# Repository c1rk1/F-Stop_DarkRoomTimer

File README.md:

# F-Stop DarkRoom Timer
Simple to build, simple to use "F-Stop" DarkRoom Timer. 
- F-Stop-s  1/1, 1/2, 1/3, 1/4, 1/6, 1/12
- Strip expo feature - 3, 5, 7, 9 strips
- Zone expo feature, from 5 to 15 zones for dodge and burn
- develop timer feature - 1-900sec (15min)

F- stop printing was originally made popular by the award winning printer Gene Nocon in 1987. 

Menu options:
*  En.-t. : Enlarger timer
*  dE.-t. : Develop timer
*  SEt.t. : Set time
*  F-St.  : f-stop set
*  Stri.  : Strip
*  Zone   : Zone expo

En.-t. : Enlarger timer - set the desired value with the rotary encoder (the steps can be set in "F-St." menu) START/Pause with the "Pedal button". Sound will be played on lamp ON and lamp OFF. Default value after power up 10 sec. (you can change it in "SEt.t." menu).

dE.-t. : Develop timer - a simple count down timer in sec. from max 900 to 0 (default after power up 180sec/ 3min) Use rotary encoder to change the value, push long (1sec) to toggle between 1x/10x. Sound will play on begin and end. Start/pause with pedal button.

SEt.t. : Set time - of the enlarger timer start/begining value (0.1-10.0)  default is 10 sec. Use the rotary encoder to change the value, short press to select and go back. This will have effect in "En.-t. : Enlarger timer" menu.

F-St.  : f-stop set - set the steps what you want to use (1/1, 1/2, 1/3, 1/4, 1/6, 1/12 This will have effect in "En.-t. : Enlarger timer" and "Stri.  : Strip" menu

Stri.  : Strip - an easy way to create test strip. First set the estimated exprosure time in "En.-t. : Enlarger timer" menu then in the "Stri.  : Strip" menu select the count of the strips you want (3, 5, 7, 9). It will display ex. "S.-5" from Strip-5. To procced, long press the rotary encoder and the display will show blinking number 1. If you are ready press pedal/START button and exprosure will be made, continue while all strip is done - according to the selected count.
So for example 5. you will have 2 under exprosure and 2 over exprosure and in the middle the estimated value in  "En.-t. : Enlarger timer" menu. Ex: you estimated 10sec in  "En.-t. : Enlarger timer" menu and selected 1/2 F-Stops in "F-St.  : f-stop" menu and S.-5 (five strips). This will be:
1. strip = 5.0sec
2. strip + 2.1sec to previous (total 7.1sec)
3. strip + 2.9sec to previous (total 10.0sec - the middle, what you selected  in  "En.-t. : Enlarger timer" menu)
4. strip + 4.1sec to previous (total 14.1sec)
5. strip + 5.9sec to previous (total 20.0sec)

After developing the paper (use dE.-t. : Develop timer) select the best exprosure time what you can set it in "En.-t. : Enlarger timer" menu.

Zone   : Zone expo is very similar in use to Strip menu but the Zones (sequences) can be select from 5-15. The total expo time will be the time selected in "En.-t. : Enlarger timer" menu and the steps will be F-Stops selected in "F-St.  : f-stop" menu.

Example: you set 20sec in  "En.-t. : Enlarger timer" menu and selected 1/2 F-Stops in "F-St.  : f-stop" menu and Z.-5 (five zone). This will be:
1. Zone = 5.0sec
2. Zone + 2.1sec to previous (total 7.1sec)
3. Zone + 2.9sec to previous (total 10.0sec)
4. Zone + 4.1sec to previous (total 14.1sec)
5. Zone + 5.9sec to previous (total 20.0sec)

The zones will help you to make dodge and burn on the print.

In the schematics I used big 1" 7-segment RED display with the 74HC595 shift registers connected to arduino 5,6,7 pins useing the ShiftDisplay library from Github. You can use any 7segment 4 digit red display what is compatible with the ShiftDisplay library.

Added support for Adafruit_LEDBackpack HT16K33 4 digit 14-Segment Display - use F-Stop_DarkRoomTimer14

* Rotary encoder connect to pins 2,3,4 and GND (A,B, button)
* START/PAUSE pedal/button connect to pin 8 and GND - simple push button or pedal or both
* Lamp controll relay board connect to pin 9 and GND - simple 5v relay board to controll the enlarger
* Piezo buzzer connect to pin 10 and GND on the arduino board.

TO DO list:
1. expand dE.-t. : Develop timer to can select minutes with seconds or seconds only and add selectable tick sound for 10,20,30 sec to use for film developing and tick sound for flip inversion remainder.

Ver. 1.02 
- Added Zone expo feature, from 5 to 15 zones for dodge and burn
  
Ver. 1.01 
- Added 1/4 F-Stop
- Added 0.1 resolution for SEt.t. : Set time menu
- bug fixed when display showed 0.0 instead of 10.0 when e_time variable was 9.9999942

Ver. 1.00 - initial relase

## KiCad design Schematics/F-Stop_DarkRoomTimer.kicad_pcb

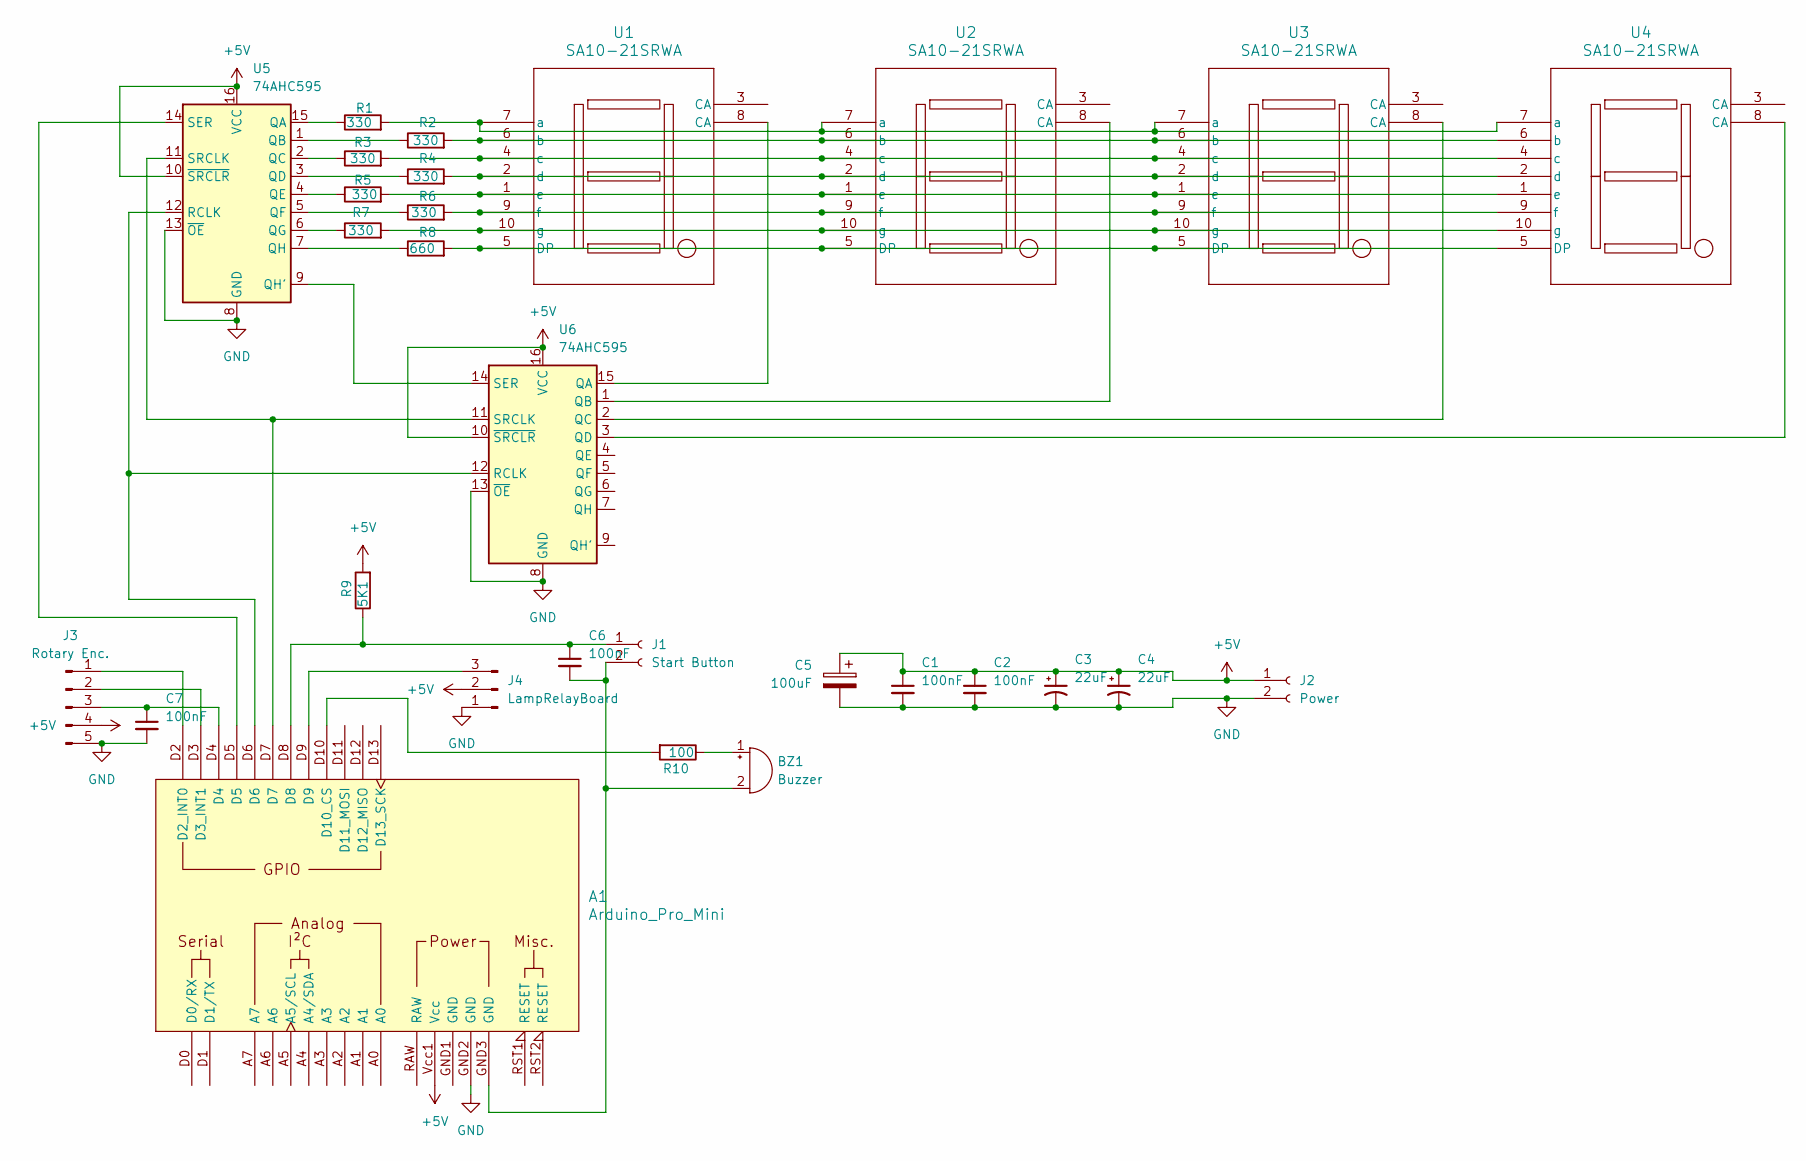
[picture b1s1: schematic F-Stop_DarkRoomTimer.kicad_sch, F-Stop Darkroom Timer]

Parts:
A1: Arduino_Pro_Mini; Clone_Pro_Mini_Socket_NoSPH
BZ1: Buzzer; Buzzer_TDK_PS1240P02BT_D12.2mm_H6.5mm
C1, C2, C6, C7: 100nF; C_0805_2012Metric_Pad1.18x1.45mm_HandSolder; Voltage 1kV; Tolerance 100%
C3, C4: 22uF; C_1812_4532Metric_Pad1.57x3.40mm_HandSolder; Voltage 1kV; Tolerance 100%
C5: 100uF; CP_Radial_D5.0mm_P2.00mm
J1: Start Button; PinHeader_1x02_P2.54mm_Vertical
J2: Power; PinHeader_1x02_P2.54mm_Vertical
J3: Rotary Enc.; PinHeader_1x05_P2.54mm_Vertical
J4: LampRelayBoard; PinHeader_1x03_P2.54mm_Vertical
R1, R2, R3, R4, R5, R6, R7: 330; R_0805_2012Metric_Pad1.15x1.40mm_HandSolder
R8: 660; R_0805_2012Metric_Pad1.15x1.40mm_HandSolder
R9: 5K1; R_0805_2012Metric_Pad1.15x1.40mm_HandSolder
R10: 100; R_0805_2012Metric_Pad1.15x1.40mm_HandSolder
U1, U2, U3, U4: SA10-21SRWA; SA10-21SRWA_KNB
U5, U6: 74AHC595; SOIC-16_3.9x9.9mm_P1.27mm

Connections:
+5V: A1.Vcc1 (Vcc), C1.1, C2.1, C3.1, C4.1, C5.1, J2.1, J3.4 (Vcc+), J4.2, R9.2, U5.10 (~SRCLR), U5.16 (VCC), U6.10 (~SRCLR), U6.16 (VCC)
GND: A1.GND2 (GND), C1.2, C2.2, C3.2, C4.2, C5.2, C7.2, J2.2, J3.5 (GND), J4.1, U5.8 (GND), U5.13 (~OE), U6.8 (GND), U6.13 (~OE)
unnamed: A1.D2 (D2_INT0), J3.1 (CLK)
unnamed: A1.D3 (D3_INT1), J3.2 (DT)
unnamed: A1.D10 (D10_CS), R10.2
unnamed: BZ1.1 (+), R10.1
unnamed: A1.GND3 (GND), BZ1.2 (-), C6.2, J1.2
unnamed: A1.D8, C6.1, J1.1, R9.1
unnamed: A1.D4, C7.1, J3.3 (SW)
unnamed: A1.D9, J4.3
unnamed: R8.2, U1.5 (DP), U2.5 (DP), U3.5 (DP), U4.5 (DP)
unnamed: R1.2, U1.7 (a), U2.7 (a), U3.7 (a), U4.7 (a)
unnamed: R2.2, U1.6 (b), U2.6 (b), U3.6 (b), U4.6 (b)
unnamed: R3.2, U1.4 (c), U2.4 (c), U3.4 (c), U4.4 (c)
unnamed: R4.2, U1.2 (d), U2.2 (d), U3.2 (d), U4.2 (d)
unnamed: R5.2, U1.1 (e), U2.1 (e), U3.1 (e), U4.1 (e)
unnamed: R6.2, U1.9 (f), U2.9 (f), U3.9 (f), U4.9 (f)
unnamed: R7.2, U1.10 (g), U2.10 (g), U3.10 (g), U4.10 (g)
unnamed: R1.1, U5.15 (QA)
unnamed: R2.1, U5.1 (QB)
unnamed: R3.1, U5.2 (QC)
unnamed: R4.1, U5.3 (QD)
unnamed: R5.1, U5.4 (QE)
unnamed: R6.1, U5.5 (QF)
unnamed: R7.1, U5.6 (QG)
unnamed: U5.9 (QH'), U6.14 (SER)
unnamed: R8.1, U5.7 (QH)
unnamed: A1.D6, U5.12 (RCLK), U6.12 (RCLK)
unnamed: A1.D5, U5.14 (SER)
unnamed: A1.D7, U5.11 (SRCLK), U6.11 (SRCLK)
unnamed: U1.8 (CA), U6.15 (QA)
unnamed: U2.8 (CA), U6.1 (QB)
unnamed: U3.8 (CA), U6.2 (QC)
unnamed: U4.8 (CA), U6.3 (QD)

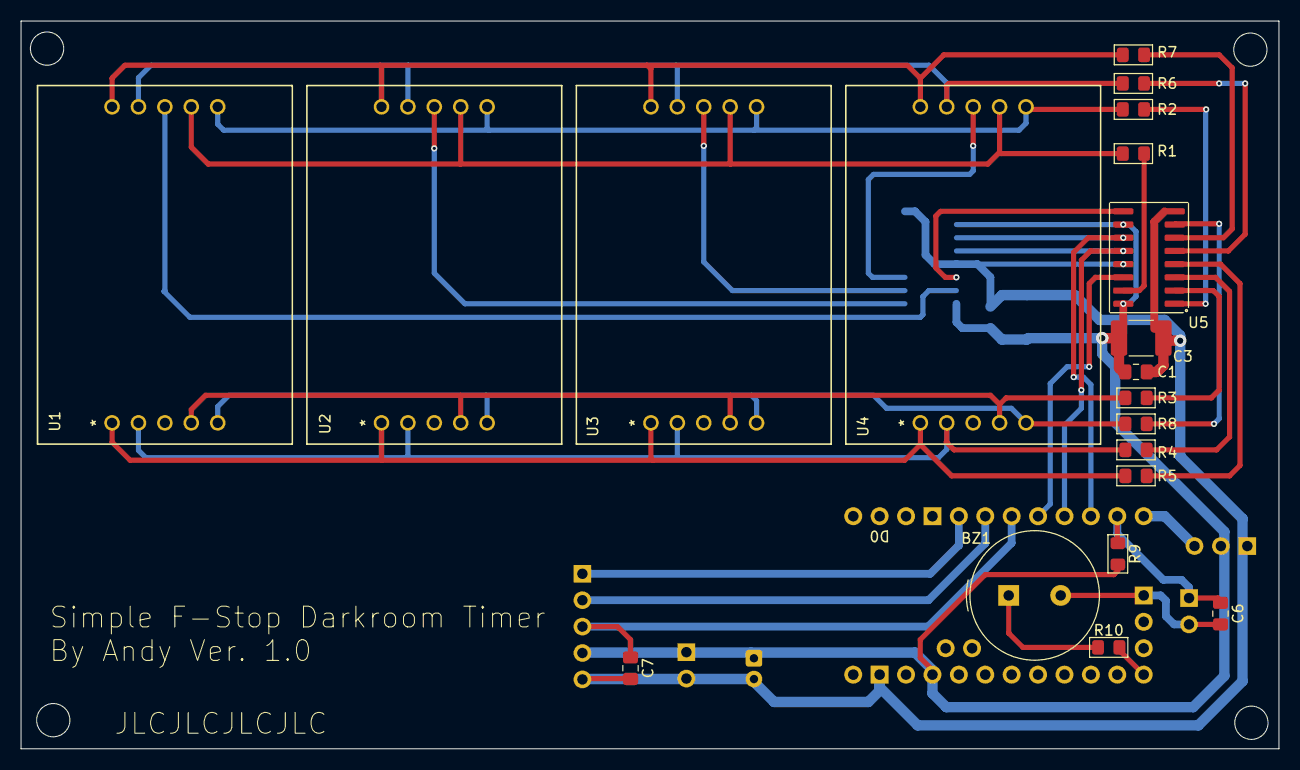
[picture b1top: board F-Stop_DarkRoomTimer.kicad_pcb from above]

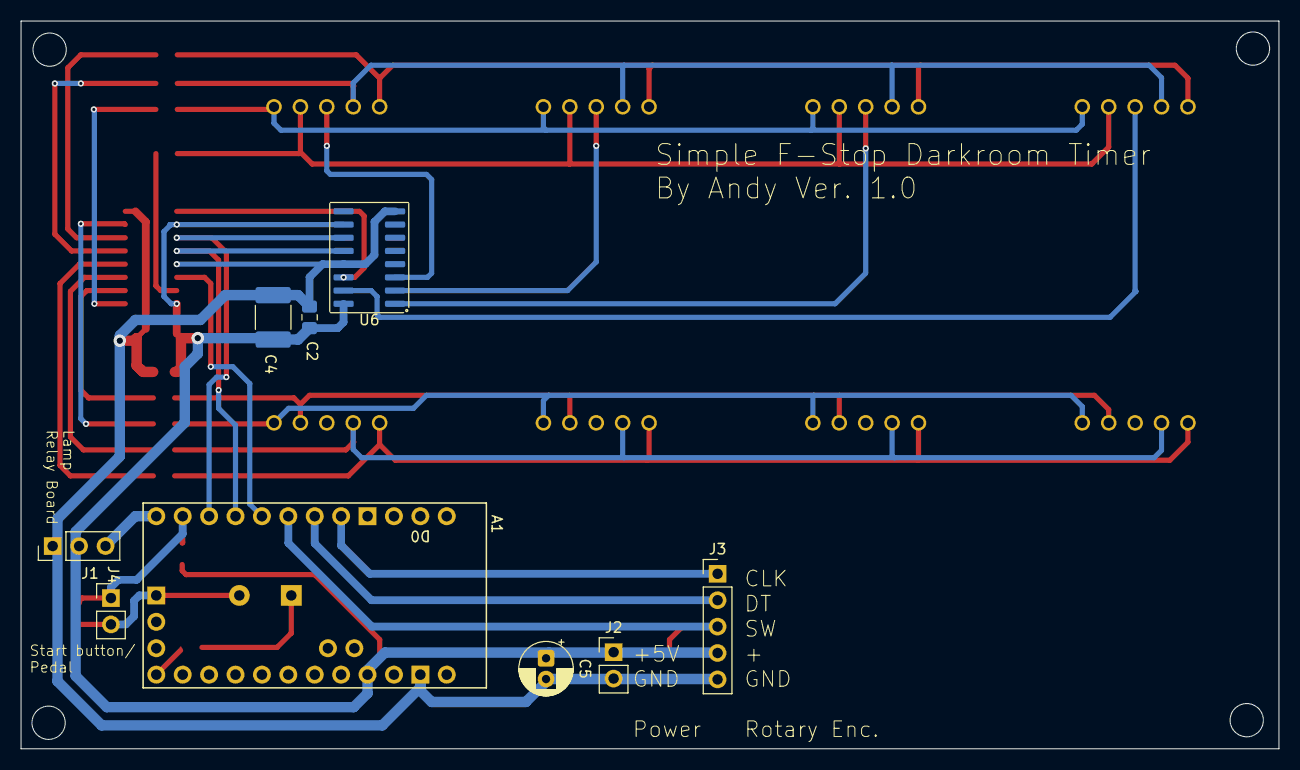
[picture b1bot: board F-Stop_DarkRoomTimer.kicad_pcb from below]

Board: 2 copper layers, 121.0 x 70.0 mm, 29 parts (9 on the bottom side), 34 nets.

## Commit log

2026-01-06 Update F-Stop_DarkRoomTimer.ino
    update to 1.01
    added 1/4 f-stop
    added set time in 0.1 resolution
2026-01-06 Update README.md
    updated to Ver. 1.01
2026-01-07 Update F-Stop_DarkRoomTimer.ino
    upgrade to ver. 1.02
    added Zone feature
2026-01-07 Update README.md
    update to 1.02
    Added Zone expo feature
2026-02-26 Update README.md
    added support for HT16K33
